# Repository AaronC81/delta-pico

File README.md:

# Delta Pico

The Delta Pico is a **powerful scientific calculator built around the Raspberry
Pi Pico**.

![Three images of the Delta Pico calculator on a wooden surface. The first shows the menu interface,
with a list of applications such as Calculator and Graph. The second shows the Calculator app, with
an expression being edited. The third shows the Graph app, with a parabolic graph plot.](img/table.jpg)

A follow-on project from my [Delta
M0](https://github.com/AaronC81/delta-m0), this calculator is much larger
and significantly more capable, with a 2.8" 240x320 colour display and 30 keys.

The Delta Pico is powered by the [rbop](https://github.com/AaronC81/rbop)
mathematical engine, for gorgeous textbook-style input.

The Delta Pico's software is written in Rust. The hardware abstraction layer is
separate to the user software, theoretically allowing the operating system to
run on other hardware which supports embedded Rust!

![Ferris, the Rust mascot, a crab, sitting on top of the Delta
Pico](img/ferris.jpg)

## Building

### Dependencies

You will likely need a bleeding-edge checkout of rbop, so you should check this
out too and adjust the path in `rust/Cargo.toml` accordingly.

This project has a dependency on FontForge, which is used for compiling fonts
into bitmaps. Install FontForge, and then set the `DELTA_PICO_FFPYTHON`
environment variable to point to its included `ffpython` executable. If you've
done this right, you should be able to run `$DELTA_PICO_FFPYTHON` in your 
terminal (or `%DELTA_PICO_FFPYTHON%` on Windows) and get a Python interactive
prompt.

The build script also uses [elf2uf2-rs](https://github.com/JoNil/elf2uf2-rs) to
flash software to the Pico, so be sure to install this.

### Building and Flashing

With all of the above dependencies sorted, cd into `rust-hal` and run:

```
cargo run
```

With a Pico connected in bootloader mode, this should build the project and
flash it onto your Pico.

## Hardware

The KiCad files for the Delta Pico hardware can be found in the `cad` directory.

There is one error with the first hardware revision; a missing trace in the
button matrix, between the down arrow button and diode D8. This can be easily
fixed with a small piece of wire:

![A small piece of wire between the down arrow button and diode
D8.](img/wire-fix.png)

## Changelog
### Revision 1
- Initial revision!

### Revision 2
- Add I2C EEPROM chip
- Fix missing trace from "down" button to diode
- Connect display SD pins
- Move Pico further to the side to accommodate SD pins
- Rotate and move expansion socket to not be behind the display

### Revision 3
- Migrate to KiCad 6
- Button layout tweaks
    - The `(` key has been removed and merged into the `)` key to form a single `( )` key
        - rbop treats brackets as a block element, so it isn't possible to have a non-paired
          bracket
        - This means there is no reason to have a separate key for each bracket
    - In place of the `(` key, there is a new `TEXT` key
        - This will be used to toggle a multi-tap text entry mode on the numeric keypad
- Replace the expansion socket with a new debug port
    - 8 pins (4x2) rather than 4 pins
    - 2 of the extra pins are SWCLK and SWDIO (marked SWC and SWD respectively)
    - Other 2 are GPIO 18 and GPIO 19, currently unused
    - Moved to not be in the way of SD card slot
- Connect PCF8574 interrupt pins to GPIO 16/17
- Power-related tweaks
    - Broken out VSYS and GND near the JST battery connector
    - Add MOSFET to allow Pico to turn display on/off
        - Gate controllable with GPIO 22
    - Connect power switch to 3V3 and two GPIOs instead
        - The Pico is now always drawing battery power through VSYS
        - GPIO 26 or 27 will be high in the switch's on or off position respectively
        - In future, the device will soft-power-off by having the Pico turn off the display and
          enter DORMANT mode
    - Add Schottky diode on VSYS, to comply with the datasheet's suggestion

## License

This repository is licensed entirely under the [MIT License](LICENSE), except
for `font/DroidSans.ttf`, which is sourced from Adobe Fonts and licensed under
the [Apache License](https://fonts.adobe.com/variations/1291/eula).

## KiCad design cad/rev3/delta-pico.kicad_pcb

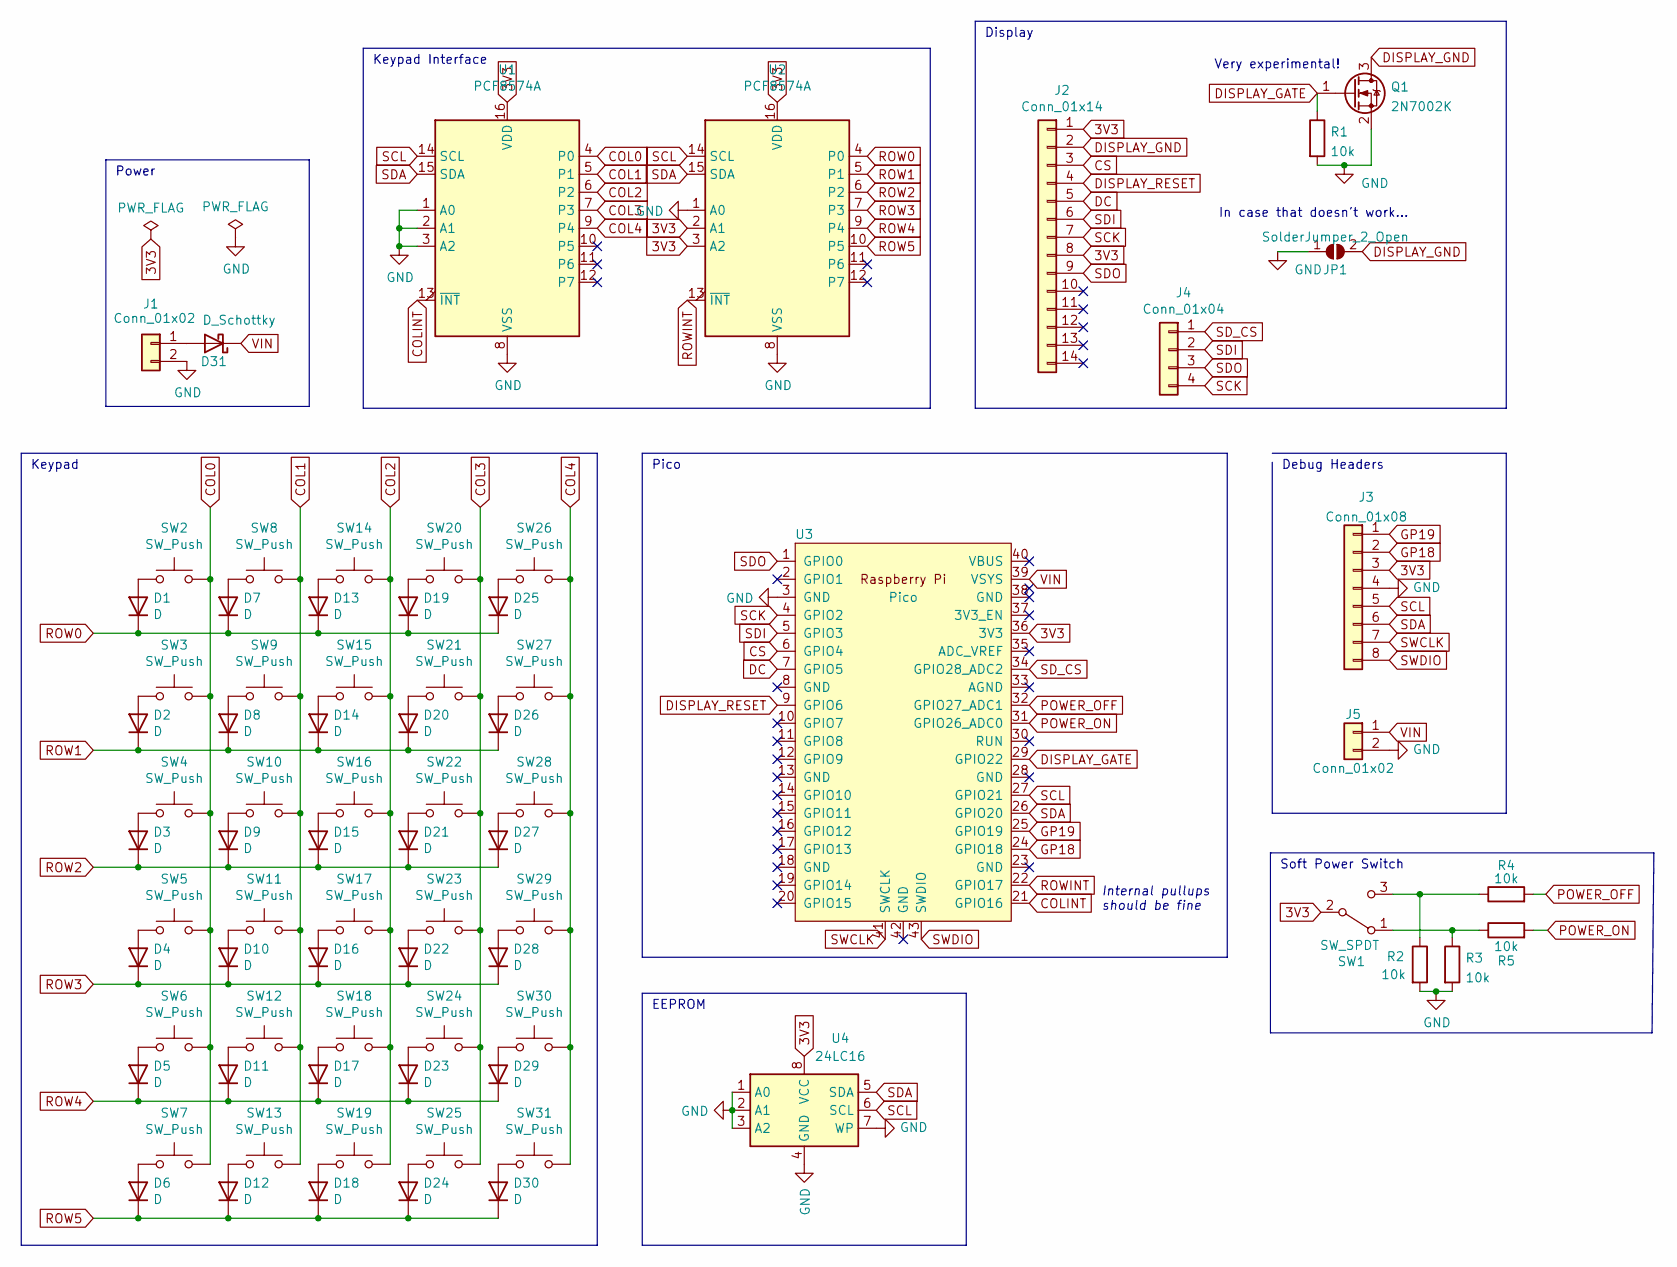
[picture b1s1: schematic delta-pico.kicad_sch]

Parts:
D1, D2, D3, D4, D5, D6, D7, D8, D9, D10, D11, D12, D13, D14, D15, D16, D17, D18, D19, D20, D21, D22, D23, D24, D25, D26, D27, D28, D29, D30: D; D_SOD-123
D31: D_Schottky; D_SOD-123
J1: Conn_01x02; JST_PH_S2B-PH-K_1x02_P2.00mm_Horizontal
J2: Conn_01x14; PinHeader_1x14_P2.54mm_Vertical
J3: Conn_01x08; PinHeader_2x04_P2.54mm_Vertical
J4: Conn_01x04; PinHeader_1x04_P2.54mm_Vertical
J5: Conn_01x02; PinHeader_1x02_P2.54mm_Vertical
JP1: SolderJumper_2_Open; SolderJumper-2_P1.3mm_Open_RoundedPad1.0x1.5mm
Q1: 2N7002K; SOT-23
R1, R2, R3, R4, R5: 10k; R_0603_1608Metric_Pad0.98x0.95mm_HandSolder
SW1: SW_SPDT; SW_SPDT_CK-JS102011SAQN
SW2, SW3, SW4, SW5, SW6, SW7, SW8, SW9, SW10, SW11, SW12, SW13, SW14, SW15, SW16, SW17, SW18, SW19, SW20, SW21, SW22, SW23, SW24, SW25, SW26, SW27, SW28, SW29, SW30, SW31: SW_Push; PTS636SL43LFS
U1, U2: PCF8574A; SOIC-16W_7.5x10.3mm_P1.27mm
U3: Pico; RPi_Pico_SMD_TH
U4: 24LC16; SOIC-8_3.9x4.9mm_P1.27mm

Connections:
3V3: J2.1, J2.8, J3.3, SW1.2 (B), U1.16 (VDD), U2.2 (A1), U2.3 (A2), U2.16 (VDD), U3.36 (3V3), U4.8 (VCC)
COL0: SW2.2, SW3.2, SW4.2, SW5.2, SW6.2, SW7.2, U1.4 (P0)
COL1: SW8.2, SW9.2, SW10.2, SW11.2, SW12.2, SW13.2, U1.5 (P1)
COL2: SW14.2, SW15.2, SW16.2, SW17.2, SW18.2, SW19.2, U1.6 (P2)
COL3: SW20.2, SW21.2, SW22.2, SW23.2, SW24.2, SW25.2, U1.7 (P3)
COL4: SW26.2, SW27.2, SW28.2, SW29.2, SW30.2, SW31.2, U1.9 (P4)
COLINT: U1.13 (~INT), U3.21 (GPIO16)
CS: J2.3, U3.6 (GPIO4)
DC: J2.5, U3.7 (GPIO5)
DISPLAY_GATE: Q1.1 (G), R1.1, U3.29 (GPIO22)
DISPLAY_GND: J2.2, JP1.2 (B), Q1.3 (D)
DISPLAY_RESET: J2.4, U3.9 (GPIO6)
GND: J1.2, J3.4, J5.2, JP1.1 (A), Q1.2 (S), R1.2, R2.2, R3.2, U1.1 (A0), U1.2 (A1), U1.3 (A2), U1.8 (VSS), U2.1 (A0), U2.8 (VSS), U3.3 (GND), U4.1 (A0), U4.2 (A1), U4.3 (A2), U4.4 (GND), U4.7 (WP)
GP18: J3.2, U3.24 (GPIO18)
GP19: J3.1, U3.25 (GPIO19)
unnamed: D1.2 (A), SW2.1
unnamed: D2.2 (A), SW3.1
unnamed: D3.2 (A), SW4.1
unnamed: D4.2 (A), SW5.1
unnamed: D5.2 (A), SW6.1
unnamed: D6.2 (A), SW7.1
unnamed: D7.2 (A), SW8.1
unnamed: D8.2 (A), SW9.1
unnamed: D9.2 (A), SW10.1
unnamed: D10.2 (A), SW11.1
unnamed: D11.2 (A), SW12.1
unnamed: D12.2 (A), SW13.1
unnamed: D13.2 (A), SW14.1
unnamed: D14.2 (A), SW15.1
unnamed: D15.2 (A), SW16.1
unnamed: D16.2 (A), SW17.1
unnamed: D17.2 (A), SW18.1
unnamed: D18.2 (A), SW19.1
unnamed: D19.2 (A), SW20.1
unnamed: D20.2 (A), SW21.1
unnamed: D21.2 (A), SW22.1
unnamed: D22.2 (A), SW23.1
unnamed: D23.2 (A), SW24.1
unnamed: D24.2 (A), SW25.1
unnamed: D25.2 (A), SW26.1
unnamed: D26.2 (A), SW27.1
unnamed: D27.2 (A), SW28.1
unnamed: D28.2 (A), SW29.1
unnamed: D29.2 (A), SW30.1
unnamed: D30.2 (A), SW31.1
unnamed: D31.2 (A), J1.1
unnamed: R3.1, R5.1, SW1.1 (A)
unnamed: R2.1, R4.1, SW1.3 (C)
POWER_OFF: R4.2, U3.32 (GPIO27_ADC1)
POWER_ON: R5.2, U3.31 (GPIO26_ADC0)
ROW0: D1.1 (K), D7.1 (K), D13.1 (K), D19.1 (K), D25.1 (K), U2.4 (P0)
ROW1: D2.1 (K), D8.1 (K), D14.1 (K), D20.1 (K), D26.1 (K), U2.5 (P1)
ROW2: D3.1 (K), D9.1 (K), D15.1 (K), D21.1 (K), D27.1 (K), U2.6 (P2)
ROW3: D4.1 (K), D10.1 (K), D16.1 (K), D22.1 (K), D28.1 (K), U2.7 (P3)
ROW4: D5.1 (K), D11.1 (K), D17.1 (K), D23.1 (K), D29.1 (K), U2.9 (P4)
ROW5: D6.1 (K), D12.1 (K), D18.1 (K), D24.1 (K), D30.1 (K), U2.10 (P5)
ROWINT: U2.13 (~INT), U3.22 (GPIO17)
SCK: J2.7, J4.4, U3.4 (GPIO2)
SCL: J3.5, U1.14 (SCL), U2.14 (SCL), U3.27 (GPIO21), U4.6 (SCL)
SDA: J3.6, U1.15 (SDA), U2.15 (SDA), U3.26 (GPIO20), U4.5 (SDA)
SDI: J2.6, J4.2, U3.5 (GPIO3)
SDO: J2.9, J4.3, U3.1 (GPIO0)
SD_CS: J4.1, U3.34 (GPIO28_ADC2)
SWCLK: J3.7, U3.41 (SWCLK)
SWDIO: J3.8, U3.43 (SWDIO)
VIN: D31.1 (K), J5.1, U3.39 (VSYS)

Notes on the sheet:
Internal pullups should be fine
Display
Very experimental!
Keypad Interface
In case that doesn't work...
Pico
Soft Power Switch
Power
EEPROM
Debug Headers
Keypad

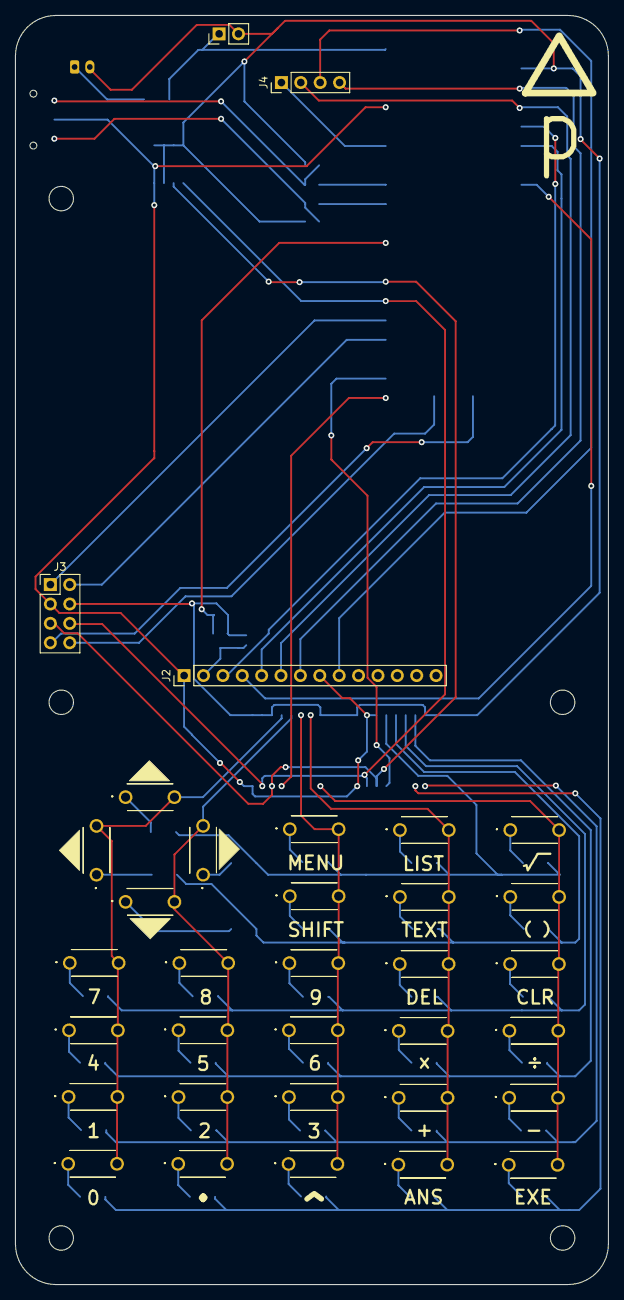
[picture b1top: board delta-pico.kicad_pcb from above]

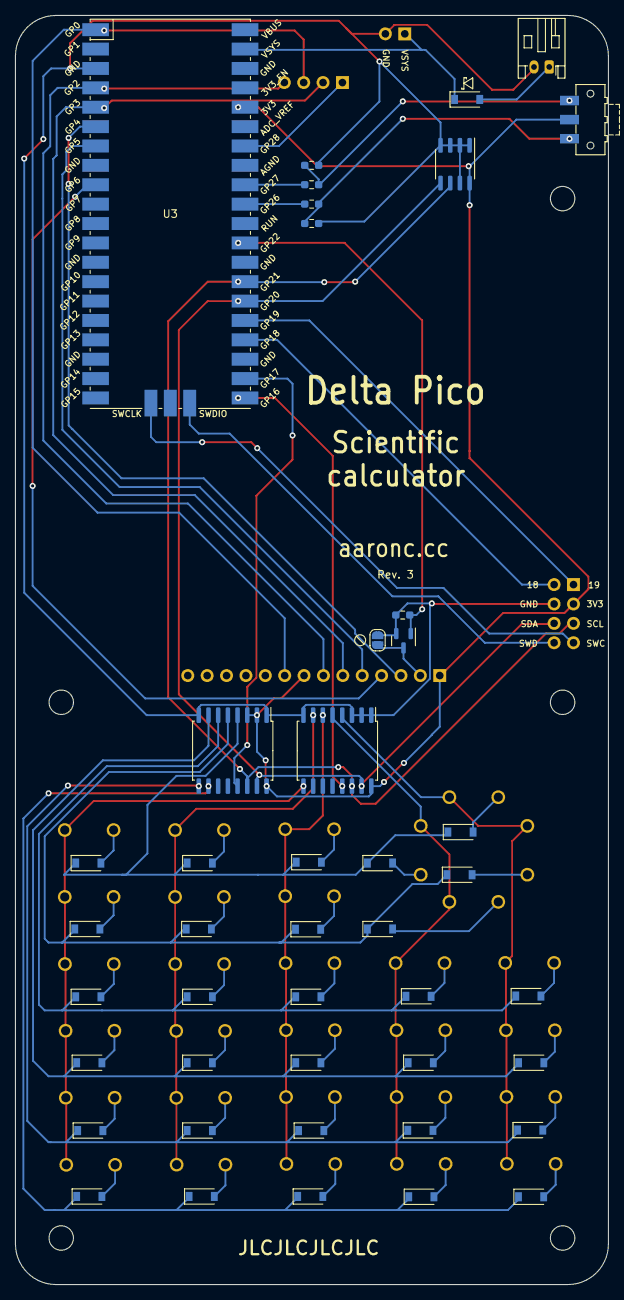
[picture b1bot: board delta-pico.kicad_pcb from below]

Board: 2 copper layers, 77.7 x 166.3 mm, 78 parts (44 on the bottom side), 66 nets.

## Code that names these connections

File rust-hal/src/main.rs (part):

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    pac,
    sio::{Sio, SioFifo, Spinlock},
    watchdog::Watchdog,
    spi::{Spi, SpiDevice}, gpio::{FunctionSpi, PinId, FunctionI2C, Pin, bank0::{Gpio20, Gpio21}}, I2C, Timer, multicore::{Stack, Multicore},
}, pac::I2C0};

#[global_allocator]
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/// Stored in a global so that core 1 can access it too - the HAL doesn't seem to provide a method
/// to get access to an I2C peripheral without re-initialising it, so it can't be stolen like most
/// other peripherals can.
static mut I2C: Option<&'static mut I2C<I2C0, (Pin<Gpio20, FunctionI2C>, Pin<Gpio21, FunctionI2C>)>> = None;

/// A spinlock with an arbitrarily-chosen number, used to sychronise access to the I2C bus.
type I2CSpinlock = Spinlock<8>;
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    led.set_high().unwrap();

    // Chip-select display
    let mut cs_pin = pins.gpio4.into_push_pull_output();
    cs_pin.set_low().unwrap();

    // Set up SPI and pins
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        70_000_000.Hz(),
        &MODE_0,
    );
    let _miso = pins.gpio0.into_mode::<FunctionSpi>();
    let _mosi = pins.gpio3.into_mode::<FunctionSpi>();
    let _sclk = pins.gpio2.into_mode::<FunctionSpi>();

    // Hardware reset
    let mut rst_pin = pins.gpio6.into_push_pull_output();
    rst_pin.set_low().unwrap();
    delay.delay_ms(50);
    rst_pin.set_high().unwrap();
    delay.delay_ms(50);

    // DC pin
    let dc_pin = pins.gpio5.into_push_pull_output();

    // Construct ILI9341 instance
    let ili = ili9341::Ili9341::new(
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    ).init().unwrap();

    // Construct PCF8574 instances
    let sda_pin = pins.gpio20.into_mode::<FunctionI2C>();
    let scl_pin = pins.gpio21.into_mode::<FunctionI2C>();
    let mut i2c = I2C::i2c0(
        pac.I2C0,
        sda_pin,
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
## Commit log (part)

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2021-11-07 Allow bitmaps to be drawn
2021-11-07 Fix About app drawing non-existent bitmap
2021-11-07 Add API for getting battery charge remaining
2021-11-07 Add battery/USB power readout
2021-11-11 Allow application list to be scrolled
    Temporarily added duplicates of some apps for demo
2021-11-12 Add unfinished 2048 clone
    No scoring, and panics if you lose
2021-11-12 Draw text in middle of tiles
2021-11-12 Rename to 2048, add icon, make icon lookup more robust
2021-11-12 Derive more on ButtonInput
2021-11-13 Implement extremely basic Tetris
2021-11-13 Hide Real Time Test and reorder applications
2021-11-15 Add hardware changelog
2021-11-15 Update revision number silkscreen
2021-11-15 Real Mac hours
2021-11-15 Fix footprint for new relative library path
2021-11-15 Fix a lot of DRC errors
2021-11-15 Remove pointless via
2021-11-15 Connect PCF8574 interrupt pins to GPIO 16/17
2021-11-16 More ignore
2021-11-16 Add 3D model for buttons
2021-11-16 Make board longer for extra mounting holes, tidy up Edge.Cuts
2021-11-17 Pico calls it VSYS, not VIN
2021-11-20 Add proof-of-concept T9 typing
2021-11-21 It's called multi-tap, not T9, when it isn't predictive
2021-11-21 Replace ButtonInput with OSInput for applications
    Allows Rust-style enum to be used for input
    This will be used for multi-tap
2021-11-21 Add multi-tap implementation to input API
    New OSInputs for new or cycled characters
2021-11-21 Fix character width
2021-11-21 Split up interface.rs into files
2021-11-21 Make most drawing methods private, add Colour type
2021-11-21 Make rest of raw display functions private
2021-11-21 Fix erroneous rust-analyzer warning about missing "test" crate
2021-11-22 Adjust image transparency threshold
    This makes images with rounded edges look better
2021-11-22 Add wrapping for menu item titles
2021-11-26 Add currently non-functional Settings app
2021-11-27 Begin adding settings storage system
2021-11-27 Update title bar according to settings
2021-11-27 Add run-length encoding for images
    Frees up about 15kB across all images
2021-11-27 Fix up wrapping on menus smaller than the screen
2021-11-27 Display nice panic message on Rust side Also enables text wrapping of words longer than a line
2021-12-02 Add MOSFET for display power control
    And if that doesn't work, there's a jumper to bypass it
2021-12-10 VERY early stages of moving to Pico SDK
    It boots, and the display works, but currently just shows a square
2021-12-20 Slow down I2C bus, 1MHz is way too fast for PCF8574
2021-12-20 Add CMake autocomplete
2021-12-20 Fix colours by fixing byte order, add bitmap drawing
2021-12-20 Fix flipped pixels
2021-12-21 Ignore __pycache__
2021-12-21 Bounds check drawPixel
2021-12-21 Fix character spacing
    Why is this off-by-one? I have no idea!
2021-12-21 Fix anti-aliasing against non-black backgrounds
2021-12-21 Add battery voltage reading
    Incorrect on Rev.3 due to Schottky, will fix that later
2021-12-21 Implement debugHandler
    Now that serial is so much more reliable!
2021-12-21 Fix calculator history sprites
2021-12-22 Big refactor
    - Remove animate.hpp, unused for ages
    - Remove application_framework, no longer needed as apps are Rust
    - Fix CAT24C (for real this time!)
    - Clean up sprite destructor
    - Use lambdas for ApplicationFrameworkInterface members
2021-12-22 Add line drawing
2021-12-22 Tidy USB descriptors file
2021-12-22 Don't draw rectangle outlines yet
    Without this change, dialogs and menus are invisible
2021-12-22 Rename block num/size constants
2021-12-22 Use our own PID and VID!
    Thanks pid.codes :)
    Also rename hardware.hpp to hardware.h
2021-12-23 Add prettier mass storage screen, allow DEL to stop
2021-12-23 Add a graphics benchmark
2021-12-23 Optimise text anti-aliasing calculation
    Roughly 16% faster to render text on benchmark (298k -> 250k)
2021-12-23 Optimise drawing fully opaque font pixels
    Text benchmark 250k -> 217k
2021-12-24 Make this a CDC device as well
    Not having a serial console for debugging is getting annoying!
    I'll try to get printf working at some point.
    Currently this just screams whenever MSC is active
2021-12-24 Remove debug print
2021-12-24 Implement debug_handler for new CDC
2021-12-24 Show a splash screen while loading storage
2021-12-24 Update storage icon and name
2021-12-24 Add a very basic Files app
2021-12-26 Add TODO
2021-12-27 Remove sleep which didn't actually need to be there
2021-12-27 Remove Tetris and RealTimeApplication
    Tetris was very incomplete, and RealTimeApplication has limited use
2021-12-27 Polish revision definitions, add trait for Schottky voltage drop
2021-12-28 Store and display node/maths errors
2021-12-28 Fix flash storage after priority implementation
    Use `Vec::leak` to stop `fat` from getting dropped
2021-12-28 Fix graph application (use lines parallel to axes)
2021-12-28 Make main.cpp indentation consistent with rest of project
2021-12-29 Add a smaller font, and the ability to switch between them
2021-12-29 Fix precedence error in fill_fast handoff logic
2021-12-29 Fix OOM when clearing memory
    Rather than allocating another buffer, recycle our existing one
2021-12-30 Fix bounds checking on sprites drawn at negative coordinates
2022-01-01 Remove expensive clone in Calculator
2022-01-05 Update cbindgen
    Need /// cbindgen:ignore for some experiments
2022-03-24 Add basic test infrastructure for Calculator
2022-03-27 Add new memory usage tracking
    Tracks everything except the screen sprite
2022-03-27 Commit crimes to clip many more calculations
    This should fix OOMs when scrolling up large calculator histories
2022-03-29 Move tests into their own module, and add more
2022-03-29 Ignore cortex-debug files
2022-03-30 Keep track of maximum allocations
2022-03-30 Working ILI9341 Rust proof-of-concept
2022-03-31 Nice rusty ILI9341 driver
2022-03-31 Add `send_packet`
2022-03-31 Add fast display draw, remove broken rectangle drawing
2022-03-31 Add Sprite
2022-03-31 Drawing a rectangle also works
2022-03-31 Add PCF8574 driver and use it for prototype buttons
2022-04-01 Add delays to fix ILI9341
    block! doesn't block properly for writes
2022-04-01 Enable linking `rust` to `rust-hal`
2022-04-01 [WIP] Application lifetimes
2022-04-01 Make ILI9341 own peripherals
2022-04-01 Enable font builder to generate Rust
2022-04-02 Add working ApplicationList and menu
    Well, working but you can't interact with it yet
2022-04-02 90% of the way to working buttons
    Still need:
    - A keymap (everything currently works as EXE)
    - poll_event implementation
2022-04-02 Add back Bootloader app
2022-04-02 Streamline screen initialisation
2022-04-02 Add Rust bitmap generation and drawing
2022-04-02 Use correct hardware revision text
2022-04-02 Fix a few warnings
2022-04-03 Re-enable Timer module, move os_accessor
2022-04-03 Re-enable graphics benchmark
2022-04-03 Remove RawColour
    Not really necessary
2022-04-03 Fix rectangle clipping on Y axis
2022-04-03 Re-implement display panic handler
2022-04-03 Re-implement settings filesystem
    Settings don't do anything yet
2022-04-03 Re-add outline rectangle drawing
2022-04-04 [WIP] Begin moving graphics over to OS-side
2022-04-04 Remove accidentally-committed file
2022-04-04 Untested re-implementation of rbop-impl
2022-04-04 Use a crate to replace SaturatingInto
2022-04-04 Add line drawing and neater pixel handling
2022-04-04 Re-add ChunkTable and CalculationHistory
2022-04-05 Calculator nearly working!
    Calculation save and load is broken
2022-04-05 Add a basic PC simulator
2022-04-06 Remove simulator for now
    It makes Rust Analyzer unhappy to have mixed targets, I think
2022-04-06 Remove CMake project
    You served me well, Pico SDK :)
2022-04-06 Add font anti-aliasing
2022-04-06 rust-analyzer warning fix and cleanup pass
2022-04-06 Fix OS clippy lints
2022-04-06 Fix bitmap resolution always failing
    Oops
2022-04-12 Switch to RGB332 colour
    Huge memory saving, and still looks good!
2022-04-13 Add square roots
    Bit of clunk involving the cursor because we can't declare that we want end-padding, but that'll need fixes in rbop
2022-04-13 Begin scaffolding for scrolling into results
2022-04-13 Switch to a grey which shows up better in RGB332
2022-04-13 Fix multitap
2022-04-14 Updated images
2022-04-14 Add experimental button queue
2022-04-14 Make placeholders more sensibly sized
2022-06-03 Simplify evaluation results
2022-06-03 Don't panic if one button reading fails
2022-06-03 Remove some addressed TODOs
2022-06-03 Make rbop input match exhaustive
2022-06-03 Consolidate some display size magic numbers
2022-06-04 Replace raw pointers with OperatingSystemPointer
    Implements Deref(Mut) so can perform setup in Application::new without unsafe
2022-06-30 Break up graphics.rs
2022-07-01 Add `debug` back(?) to ApplicationFramework
2022-07-01 Clip results too
2022-07-01 Add virtual button presses, and app launch safety notes
2022-07-02 Add more tests and fix them
    There was different behaviour between release and debug
    Presumably due to optimisation due to messing with `application_to_tick`
    Now we just tick the application itself rather than indirectly
2022-07-02 Docs
2022-07-02 Significantly speed up calculation clearing
2022-07-03 Move calculator tests into separate module
2022-07-03 Add Catalog; new kind of menu for selecting function
2022-07-03 Add more stuff to catalog, make items nodes rather than functions
    Adds flexibility for input without hardware keypad, nice for sim
2022-07-04 Add catalog test
2022-07-04 Use nightly Rust for CI
2022-07-04 Install libxkbcommon dependency
2022-07-04 Use Ubuntu Bionic
    Latest LTS which FontForge PPA supports
2022-07-04 Remove Actions for now
    FontForge Python API seems different
2022-07-04 Add test for accuracy correction
2022-07-04 Add better bounds to `try_pixel_immutable`
    Fixes panic when `ui_input_expression` overflows viewport
2022-07-05 Fix frame time, move it and memory usage to separate panels
    Frame time now measured from input completion to os.draw() call
2022-07-05 Interpolate between graph points
2022-07-05 Enable newly-added use_floats to speed up graph drawing
    ~3x speedup to calculation phase
2022-07-05 Add missing import
2022-07-05 Explicitly recalculate graph values, and store in `Plot`s
    Gives us room to do optimisations by only recalculating slices
2022-07-05 Always make up graphs as vertical lines
    Looks much better and is faster too
2022-07-06 Refactor operating_system into multiple files
2022-07-06 Store entered scales as node trees
2022-07-06 Add ContextMenu
2022-07-06 Use new ContextMenu API everywhere
2022-07-06 Add dividers to context menu
2022-07-06 Add sprites in context menus
2022-07-07 Move cursor to the end of `ui_input_expression`
2022-07-07 Start adding tests for graph
2022-07-07 Add more graph tests
2022-07-08 [WIP] Very experimental multicore
2022-07-08 Fix overflows when drawing plots with large Ys to screen
2022-07-08 Add `recalculate_all_plots` convenience method
2022-07-08 Remove magic number for clock speed
2022-07-08 Tidy up based on lints
2022-07-08 Implement `should_run_tests`
2022-07-09 Add macro to deduplicate editing code
2022-07-10 Add some architecture docs
2022-07-10 Enable cancelling out of rbop inputs with MENU too
2022-07-10 Resume open app when selected on the menu
    Nicer UX than re-opening it
2022-07-10 Make negatives look a bit better
2022-07-11 Add a 3D-printable baseplate for rev. 3
2022-07-12 Cache screen-mapped Y positions in graph
    Waaaaay faster drawing now!
    For sin(x), 2ms for Y pan and ~45ms for X pan
2022-07-12 Install Pillow on GH Actions
2022-07-12 Use xvfb to run tests
2022-07-14 Initial implementation of graph tracing
    Very slow to pan, need to only recalculate partially
